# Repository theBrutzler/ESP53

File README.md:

# ESP53

ESP32-C5 -> ESP01

I created a board, that could fit an ESP32-C5 on a ESP-01 standard pinout. The default ESP01 programer is still working

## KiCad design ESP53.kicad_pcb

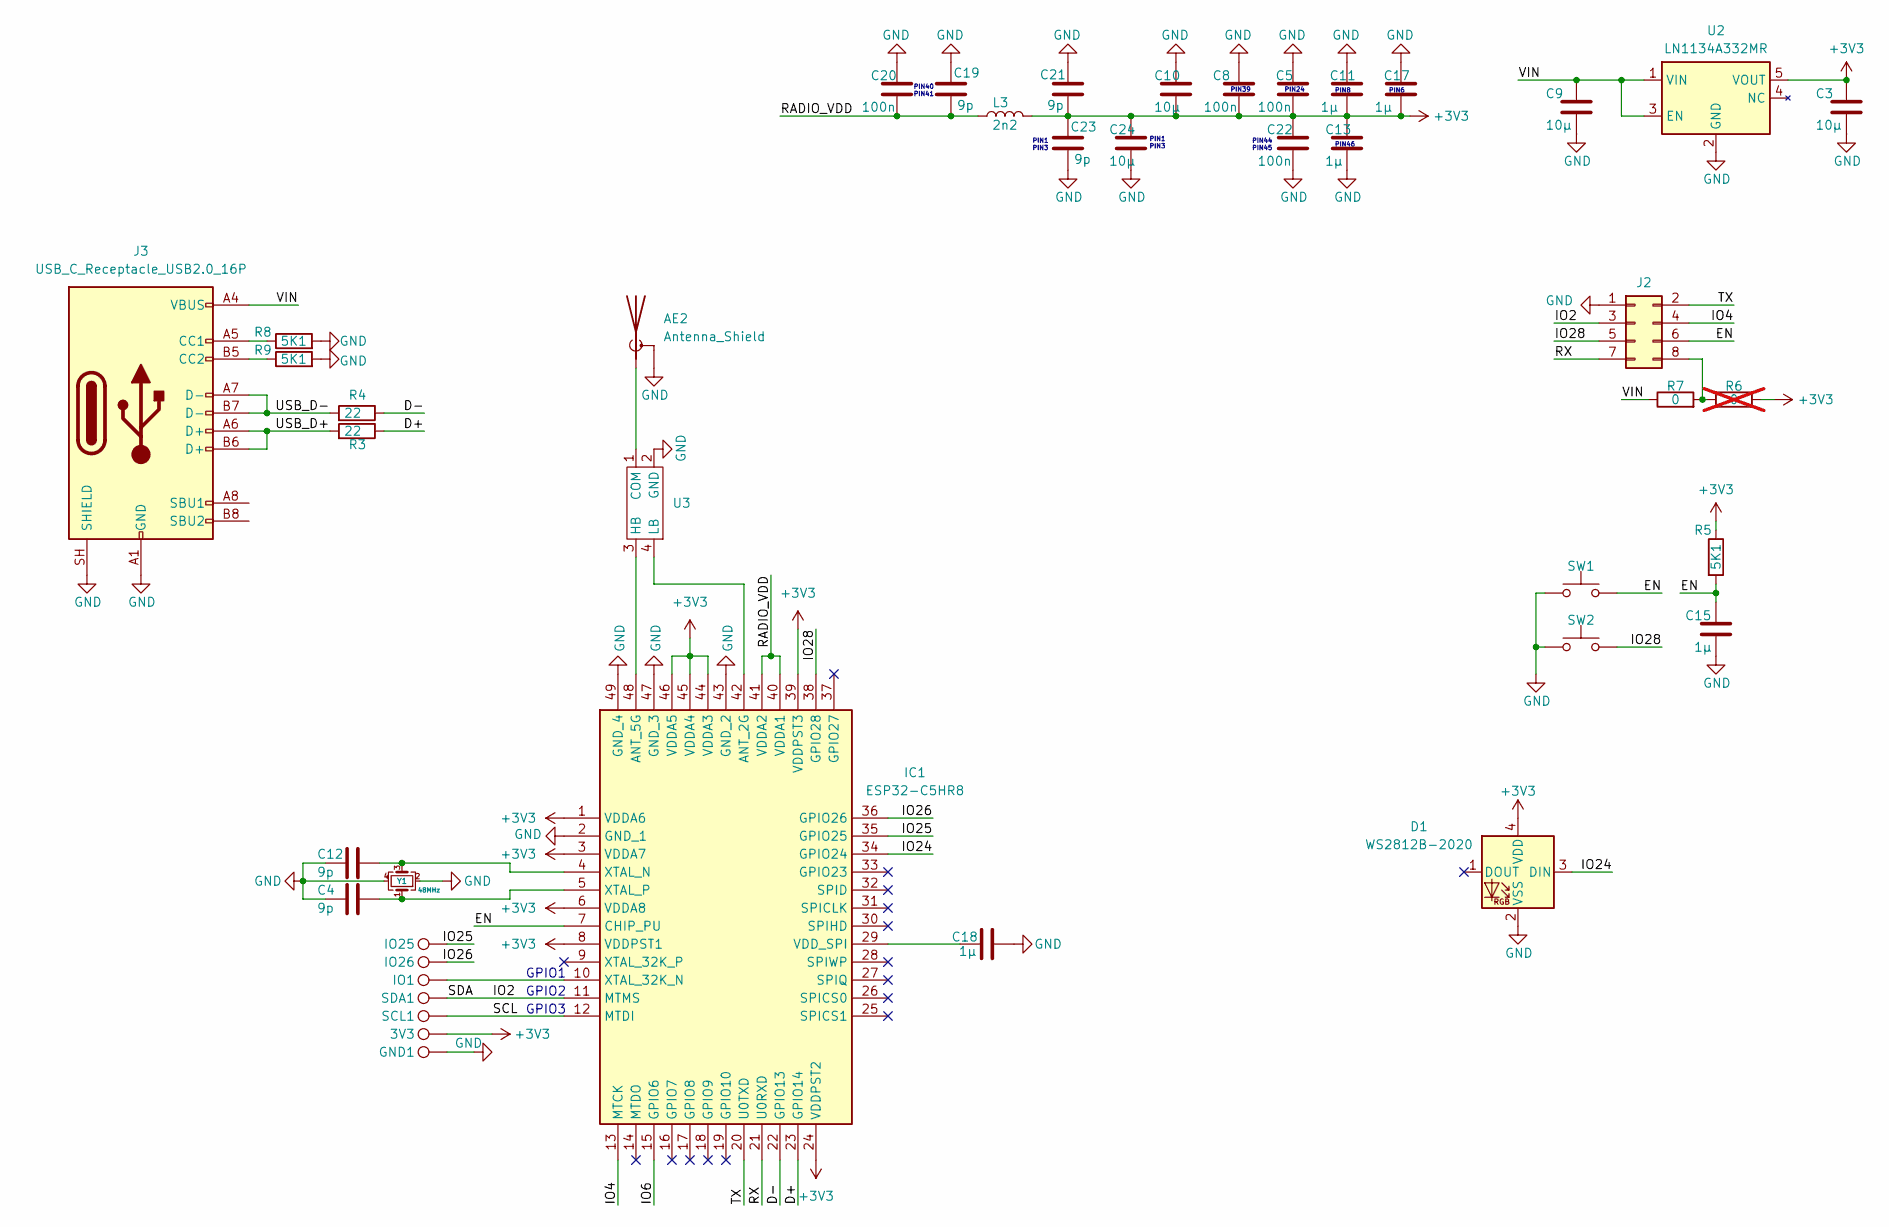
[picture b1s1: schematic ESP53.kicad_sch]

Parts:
3V3: TestPoint; TestPoint_Pad_D1.5mm
AE2: Antenna_Shield; 2065140001; LCSC C3285113
C3, C9: 10µ; R_0402_1005Metric; LCSC C315248
C4, C12, C19, C21, C23: 9p; R_0402_1005Metric; LCSC C296010
C5, C8, C20, C22: 100n; R_0402_1005Metric; LCSC C1525
C10, C24: 10µ; R_0402_1005Metric; LCSC C48543727
C11, C13, C15, C17, C18: 1µ; R_0402_1005Metric; LCSC C14445
D1: WS2812B-2020; LED_WS2812B-2020_PLCC4_2.0x2.0mm; LCSC C965556
GND1: TestPoint; TestPoint_Pad_D1.5mm
IC1: ESP32-C5HR8; QFN40P600X600X90-49N-D; Manufacturer_Part_Number ESP32-C5HR8; LCSC C51950746
IO1, IO25, IO26: TestPoint; TestPoint_Pad_D1.5mm
J2: Conn_02x04_Odd_Even; PinHeader_2x04_P2.54mm_Vertical
J3: USB_C_Receptacle_USB2.0_16P; USB_C_Receptacle_GCT_USB4105-xx-A_16P_TopMnt_Horizontal; LCSC C54308345
L3: 2n2; L_0402_1005Metric; LCSC C2941466
R3, R4: 22; R_0402_1005Metric; LCSC C25152
R5, R8, R9: 5K1; R_0402_1005Metric; LCSC C25905
R6: 0; R_0402_1005Metric; LCSC C21376; not fitted
R7: 0; R_0402_1005Metric; LCSC C21376
SCL1: TestPoint; TestPoint_Pad_D1.5mm
SDA1: TestPoint; TestPoint_Pad_D1.5mm
SW1, SW2: SW_Push; microswitch; LCSC C100056
U2: LN1134A332MR; TSOT-23-5; LCSC C141419
U3: DIPLEXER; LCSC C432970
Y1: 48MHz; Crystal_SMD_2016-4Pin_2.0x1.6mm; LCSC C50202089

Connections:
+3V3: 3V3.1 (1_1), C3.1, C5.2, C8.2, C10.2, C11.2, C13.1, C17.2, C21.2, C22.1, C23.1, C24.1, D1.4 (VDD), IC1.1 (VDDA6), IC1.3 (VDDA7), IC1.6 (VDDA8), IC1.8 (VDDPST1), IC1.24 (VDDPST2), IC1.39 (VDDPST3), IC1.44 (VDDA3), IC1.45 (VDDA4), IC1.46 (VDDA5), L3.2, R5.1, R6.2, U2.5 (VOUT)
/D+: IC1.23 (GPIO14), R3.1
/D-: IC1.22 (GPIO13), R4.1
/EN: C15.1, IC1.7 (CHIP_PU), J2.6, R5.2, SW1.2
/IO2: IC1.11 (MTMS), J2.3, SDA1.1; also elsewhere on the board
/IO4: IC1.13 (MTCK), J2.4
/IO6: IC1.15 (GPIO6)
/IO24: D1.3 (DIN), IC1.34 (GPIO24)
/IO25: IC1.35 (GPIO25), IO25.1 (1_1)
/IO26: IC1.36 (GPIO26), IO26.1 (1_1)
/IO28: IC1.38 (GPIO28), J2.5, SW2.2
/RADIO_VDD: C19.2, C20.2, IC1.40 (VDDA1), IC1.41 (VDDA2), L3.1
/RX: IC1.21 (U0RXD), J2.7
/SCL: IC1.12 (MTDI), SCL1.1; also elsewhere on the board
/TX: IC1.20 (U0TXD), J2.2
/USB_D+: J3.A6 (D+), J3.B6 (D+), R3.2
/USB_D-: J3.A7 (D-), J3.B7 (D-), R4.2
/VIN: C9.1, J3.A4 (VBUS), J3.A9 (VBUS), J3.B4 (VBUS), J3.B9 (VBUS), R7.1, U2.1 (VIN), U2.3 (EN)
GND: AE2.2 (Shield), C3.2, C4.2, C5.1, C8.1, C9.2, C10.1, C11.1, C12.2, C13.2, C15.2, C17.1, C18.1, C19.1, C20.1, C21.1, C22.2, C23.2, C24.2, D1.2 (VSS), GND1.1, IC1.2 (GND_1), IC1.43 (GND_2), IC1.47 (GND_3), IC1.49 (GND_4), J2.1, J3.A1 (GND), J3.A12 (GND), J3.B1 (GND), J3.B12 (GND), J3.SH (SHIELD), R8.2, R9.2, SW1.1, SW2.1, U2.2 (GND), U3.2 (GND), Y1.2, Y1.4; also elsewhere on the board
unnamed: AE2.1 (A), U3.1 (COM)
unnamed: IC1.42 (ANT_2G), U3.4 (LB)
unnamed: IC1.48 (ANT_5G), U3.3 (HB)
unnamed: C18.2, IC1.29 (VDD_SPI)
unnamed: IC1.10 (XTAL_32K_N), IO1.1 (1_1)
unnamed: C12.1, IC1.4 (XTAL_N), Y1.3
unnamed: C4.1, IC1.5 (XTAL_P), Y1.1
unnamed: J2.8, R6.1, R7.2
unnamed: J3.A5 (CC1), R8.1
unnamed: J3.B5 (CC2), R9.1

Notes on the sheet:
PIN39
PIN1 PIN3
GPIO3
PIN24
GPIO1
PIN8
PIN46
PIN44 PIN45
PIN40 PIN41
GPIO2
PIN6

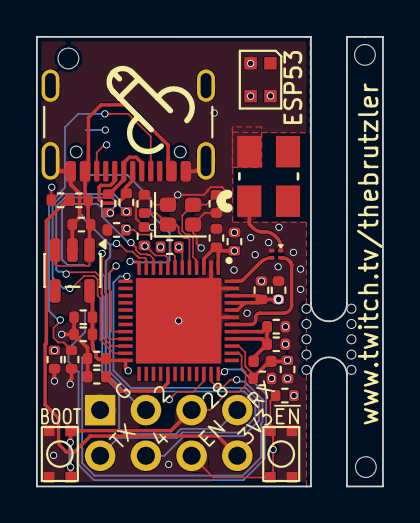
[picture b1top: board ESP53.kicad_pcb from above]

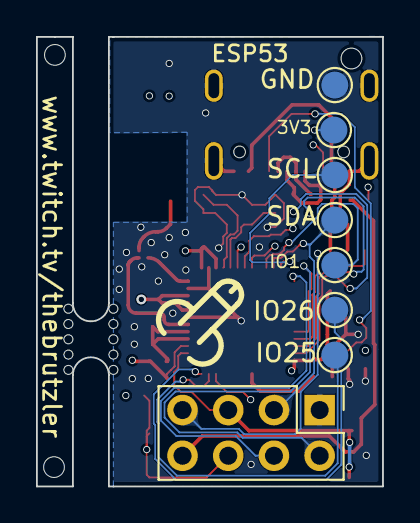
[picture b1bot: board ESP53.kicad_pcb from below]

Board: 4 copper layers, 19.2 x 25.0 mm, 43 parts (8 on the bottom side), 28 nets.

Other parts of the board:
GND: TestPoint; TestPoint_Pad_D1.5mm
SCL: TestPoint; TestPoint_Pad_D1.5mm
SDA: TestPoint; TestPoint_Pad_D1.5mm

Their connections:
/IO2: SDA.1 (1_1); also elsewhere on the board
/SCL: SCL.1 (1_1); also elsewhere on the board
GND: GND.1 (1_1); also elsewhere on the board
